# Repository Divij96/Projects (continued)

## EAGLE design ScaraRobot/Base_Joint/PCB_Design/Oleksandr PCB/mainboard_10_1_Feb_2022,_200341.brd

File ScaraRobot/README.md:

## Scara Robot
### Design and build-up of a 4 DoF SCARA like robot (3+1gripper), Intelligent machine design lab
- Mechanical models were designed using Autodesk inventor and built using 3dprinters
- The PCBs were designed using the Autodesk Eagle. They were later on manufactured
and soldered
- Each joint had an Absolute position encoder, a Torque sensor, a BLDC motor, a
gearbox, and a pair of Cross-Roller-Bearings. A master Linux PC with EtherCAT was
used for communication with the joint slaves
- The low-level control was implemented on the Microcontroller chip using C. A highlevel
control was implemented in MATLAB. EtherLab was used as a communication
interface
- The CDTM (Center for Digital Technology Management) supported us regarding the
team communication and project management aspects

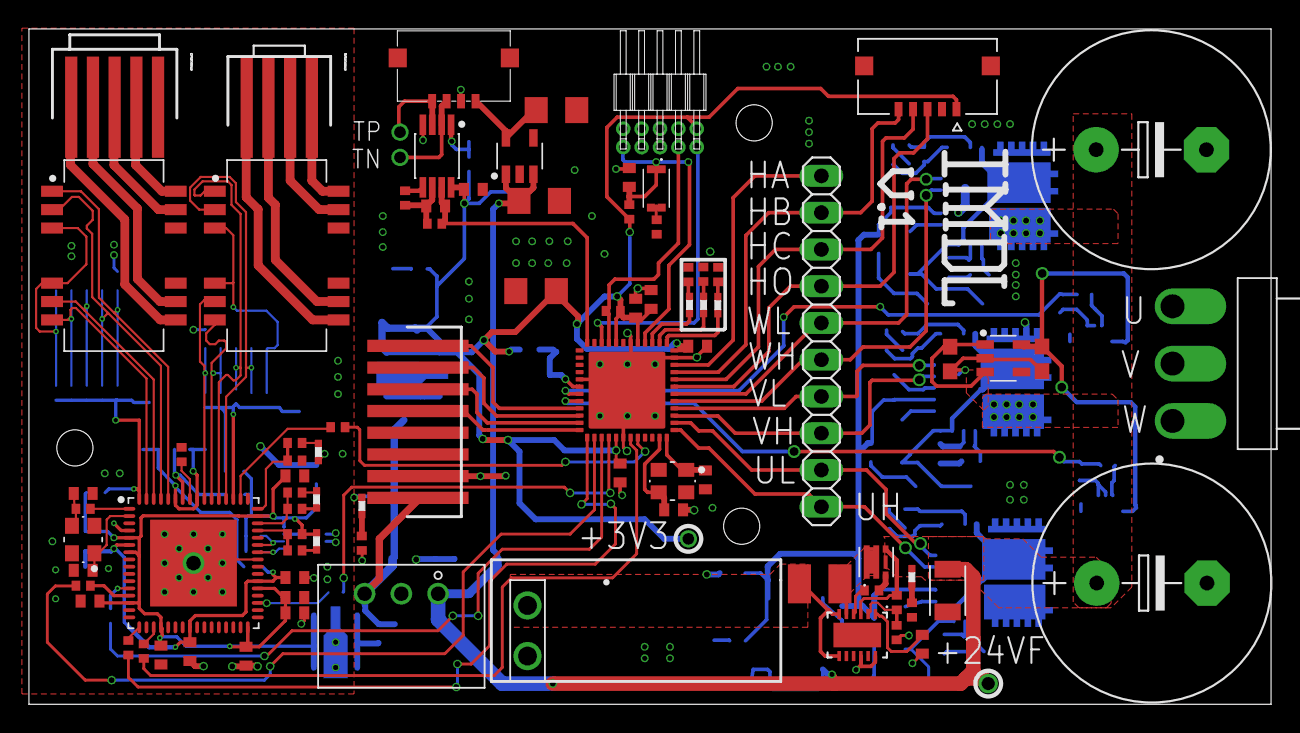
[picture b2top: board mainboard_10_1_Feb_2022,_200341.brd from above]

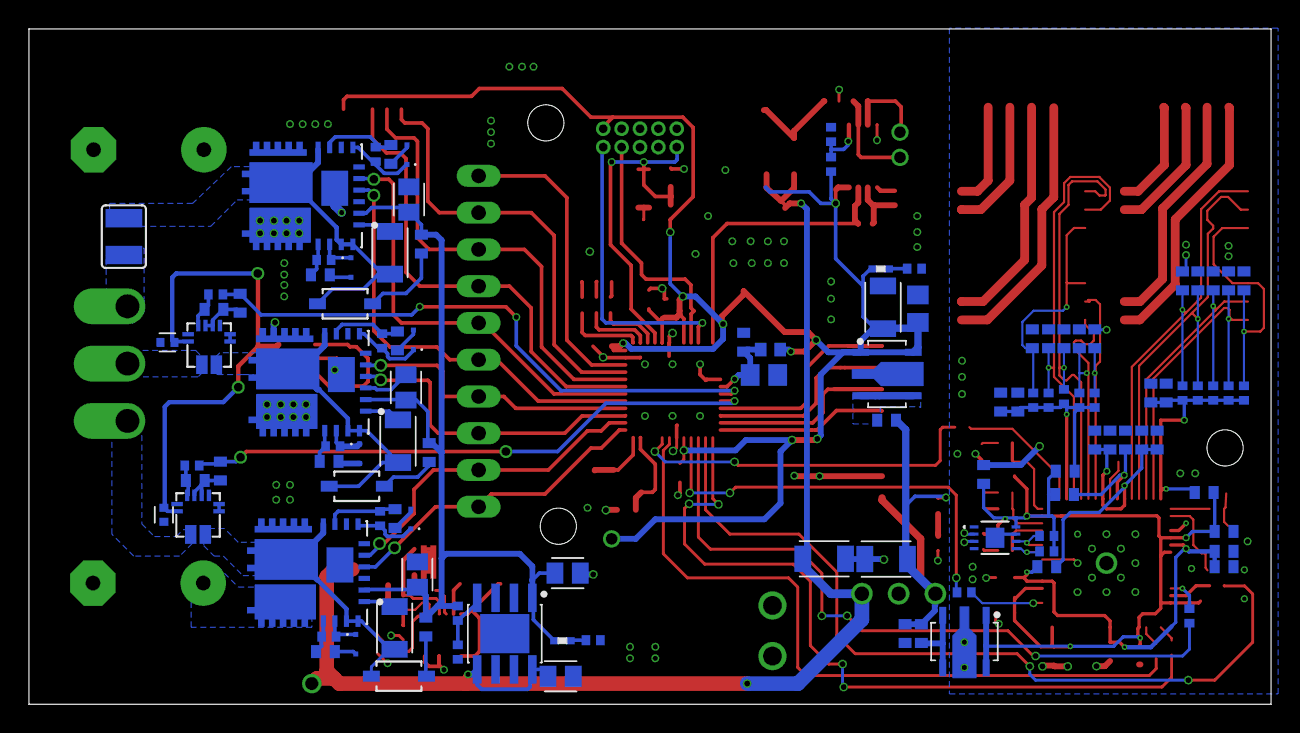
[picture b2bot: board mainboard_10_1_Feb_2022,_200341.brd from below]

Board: 2 copper layers, 85.8 x 46.7 mm, 194 parts (109 on the bottom side), 135 nets.

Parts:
AFE_TRQ1:C1: GCM155R71C683KA55; C0402
AFE_TRQ1:C2: GCM155R71C104JA55; C0402
AFE_TRQ1:IC1: MAX4208AUA+T; USOP8
AFE_TRQ1:R1: RT0402FRE07100RL; R0402
AFE_TRQ1:R2: RT0402BRD0712KL; R0402
AFE_TRQ1:R3: RT0402FRE0756KL; R0402
AFE_TRQ1:R4: RT0402BRD0710KL; R0402
ATSAMD:C4: GCM31CR71C106KA64; C1206
ATSAMD:C5, ATSAMD:C6: GCM21BR70J106KE22K; C0805
ATSAMD:C7, ATSAMD:C8, ATSAMD:C9, ATSAMD:C10, ATSAMD:C11, ATSAMD:C12: GCM155R71C104JA55; C0402
ATSAMD:C22, ATSAMD:C23: GCM1555C1H150FA16; C0402
ATSAMD:D1: QBLP595-IB; LED0402
ATSAMD:D2: QBLP595-O; LED0402
ATSAMD:D3: QBLP595-Y; LED0402
ATSAMD:IC2: ATSAMD51G18A-MUT; QFN48
ATSAMD:L1: BLM18EG221SN1D; BEADC1608X80
ATSAMD:R1, ATSAMD:R2, ATSAMD:R4: RT0402BRD0710KL; R0402
ATSAMD:R5: RT0402FRE07300RL; R0402
ATSAMD:R6: RT0402FRE0710KL; R0402
ATSAMD:R7: RT0402FRE071KL; R0402
ATSAMD:S2: USLPT2616CT2TR; USLPT2616CT
ATSAMD:Y2: ECX-2236
CURRENT_SENS:C1, CURRENT_SENS:C2: 0.1u; CAPC1005X60
CURRENT_SENS:C3, CURRENT_SENS:C4: GCM1555C1H510JA01; C0402
CURRENT_SENS:C5, CURRENT_SENS:C6: GCM155R71E223KA55; C0402
CURRENT_SENS:C7, CURRENT_SENS:C8: GCM188R71C105KA64; C0603
CURRENT_SENS:IC1, CURRENT_SENS:IC2: ACS70331EESATR-005B3; QFN12-ES
CURRENT_SENS:IC4: AP2204K-3.3TRG1; SOT-23-5
CURRENT_SENS:R3, CURRENT_SENS:R4: RT0402BRD071KL; R0402
CURRENT_SENS:SJ1: SJW
ETHERCAT1:C1, ETHERCAT1:C3, ETHERCAT1:C6, ETHERCAT1:C8, ETHERCAT1:C16: 1u; C0402
ETHERCAT1:C2, ETHERCAT1:C4, ETHERCAT1:C5, ETHERCAT1:C7, ETHERCAT1:C9, ETHERCAT1:C10, ETHERCAT1:C11, ETHERCAT1:C12, ETHERCAT1:C13, ETHERCAT1:C14, ETHERCAT1:C15, ETHERCAT1:C18, ETHERCAT1:C19, ETHERCAT1:C22: 100n; C0402
ETHERCAT1:C17: 470p; C0402
ETHERCAT1:C20, ETHERCAT1:C21: 18p; C0402
ETHERCAT1:C23, ETHERCAT1:C24, ETHERCAT1:C25, ETHERCAT1:C26, ETHERCAT1:C27, ETHERCAT1:C28, ETHERCAT1:C29, ETHERCAT1:C30: GCM1555C1H100JA16; C0402
ETHERCAT1:C31, ETHERCAT1:C32: 22n; C0402
ETHERCAT1:C33: GRM155C80J106ME11D; C0402
ETHERCAT1:C66: 1uF; C0402
ETHERCAT1:D1, ETHERCAT1:D2, ETHERCAT1:D3: QBLP595-IG; LED0402
ETHERCAT1:IC1: CAT24C512HU5IGT3; UDFN8
ETHERCAT1:IC2: RP115H331B-T1-FE; SOT-89-5
ETHERCAT1:L1, ETHERCAT1:L2, ETHERCAT1:L3, ETHERCAT1:L4, ETHERCAT1:L5: BLM15EG221SH1D; BEAD0402
ETHERCAT1:R1, ETHERCAT1:R16, ETHERCAT1:R17: 0R; R0402
ETHERCAT1:R2: 12k1; R0402
ETHERCAT1:R4, ETHERCAT1:R5: 4k7; R0402
ETHERCAT1:R6, ETHERCAT1:R24, ETHERCAT1:R25: 10k; R0402
ETHERCAT1:R7, ETHERCAT1:R26, ETHERCAT1:R27: RL1206FR-7WL; R0402
ETHERCAT1:R8, ETHERCAT1:R9, ETHERCAT1:R10, ETHERCAT1:R11, ETHERCAT1:R12, ETHERCAT1:R13, ETHERCAT1:R14, ETHERCAT1:R15: 49R9; R0402
ETHERCAT1:R18, ETHERCAT1:R19, ETHERCAT1:R20, ETHERCAT1:R21, ETHERCAT1:R22, ETHERCAT1:R23: 100; R0402
ETHERCAT1:T1, ETHERCAT1:T2: 749020100; SOIC127P965X533-16-TRAFO
ETHERCAT1:U1: LAN9252/ML; QFN64-T600
ETHERCAT1:X1: 87438-0443; 87438-04
ETHERCAT1:X3: 87438-0543; 87438-05
ETHERCAT1:Y1: ECX-2236
H1: 20021112-00010T4LF; 20021112-00010
INVERTER:C1, INVERTER:C3, INVERTER:C5: 10u 25V; CAPC2012X110
INVERTER:C2, INVERTER:C4, INVERTER:C6: 10u 50V; CAPC3216X135
INVERTER:C7, INVERTER:C8: 1mF; E7,5-16
INVERTER:CR1, INVERTER:CR2, INVERTER:CR3: 1N4148W-TPSOD123_MCC-M; SOD123_MCC-M
INVERTER:D2, INVERTER:D3, INVERTER:D4, INVERTER:D5, INVERTER:D7, INVERTER:D8: BAS3005A-02V_0; INFINEON_BAS3005A-02V_0
INVERTER:R1, INVERTER:R3, INVERTER:R7, INVERTER:R8, INVERTER:R11, INVERTER:R12: 100; R0402
INVERTER:R2, INVERTER:R4, INVERTER:R6, INVERTER:R9, INVERTER:R13, INVERTER:R15: 27; R0402
INVERTER:R5, INVERTER:R10, INVERTER:R14: 5.1; R0402
INVERTER:U$1, INVERTER:U$2, INVERTER:U$3: IRMS005-800MHTR; INFINEON_IRSM005-800MH_0
J1: 5037630591; MOLEX_5037630591
JP1: 1X10
M1: PST1,3/2-3,5; 1945096
POWER_UNIT:C1: GCM155R71E223KA55; C0402
POWER_UNIT:C2, POWER_UNIT:C3, POWER_UNIT:C4, POWER_UNIT:C6: 10u 50V; CAPC3216X135
POWER_UNIT:C5, POWER_UNIT:C9: GCM31CR71H225KA55; C1206
POWER_UNIT:C7, POWER_UNIT:C8: 2.2u; CAPC2012X110
POWER_UNIT:D1, POWER_UNIT:D2, POWER_UNIT:D3, POWER_UNIT:D4: QBLP595-IG; LED0402
POWER_UNIT:IC1: RP115H331B-T1-FE; SOT-89-5
POWER_UNIT:IC2: AP2204MP-ADJTRG1; SOIC127P600X170-9T271X340N
POWER_UNIT:IC3: AP2204K-3.3TRG1; SOT-23-5
POWER_UNIT:L5: BLM15EG221SH1D; BEAD0402
POWER_UNIT:PS2: R78E-1.0-5V; R78E-1.0
POWER_UNIT:Q1: DMN4020LFDE-7; TRANS_DMN4020LFDE-7
POWER_UNIT:R1: RT0402FRE07100RL; R0402
POWER_UNIT:R2: RT0402FRE07100KL; R0402
POWER_UNIT:R4: 10m; R1210
POWER_UNIT:R5: 11k; R0402
POWER_UNIT:R6, POWER_UNIT:R7, POWER_UNIT:R8, POWER_UNIT:R9, POWER_UNIT:R10: 1k; R0402
POWER_UNIT:R11: RT0402BRD074K99L; R0402
POWER_UNIT:U1: LT4356-1LINEAR_TECHNOLOGY_LT4356IDE-1#PBF_0_0; LINEAR_TECHNOLOGY_LT4356IDE-1#PBF_0
U$1: PTDA1,5/2-PH-3,5; 1725107
X2: B3PS-VH(LF)(SN)
X4: 87438-0843; 87438-08
X5: 5037630491

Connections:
+3V3: AFE_TRQ1:C2.1, AFE_TRQ1:IC1.8, AFE_TRQ1:R2.2, ATSAMD:C4.1, ATSAMD:C6.1, ATSAMD:C7.1, ATSAMD:C9.1, ATSAMD:C10.1, ATSAMD:C11.1, ATSAMD:IC2.17, ATSAMD:IC2.36, ATSAMD:IC2.41, ATSAMD:IC2.44, ATSAMD:L1.1, ATSAMD:R6.2, ATSAMD:R7.2, H1.1, J1.1, POWER_UNIT:C2.1, POWER_UNIT:D3.2, POWER_UNIT:IC1.1, POWER_UNIT:IC1.5
+5V: ETHERCAT1:C66.1, ETHERCAT1:L5.1, POWER_UNIT:C4.1, POWER_UNIT:D2.2, POWER_UNIT:L5.1, POWER_UNIT:PS2.3, X4.1
+5V_TRQ: POWER_UNIT:C9.1, POWER_UNIT:IC3.5, X5.1
+15V: INVERTER:C1.2, INVERTER:C3.2, INVERTER:C5.2, INVERTER:R5.2, INVERTER:R10.2, INVERTER:R14.2, INVERTER:U$1.2, INVERTER:U$2.2, INVERTER:U$3.2, POWER_UNIT:C8.1, POWER_UNIT:D4.2, POWER_UNIT:IC2.1, POWER_UNIT:R5.2
+24V: M1.1, POWER_UNIT:R4.2, POWER_UNIT:U1.6, POWER_UNIT:U1.7
+24V_F: CURRENT_SENS:C8.1, CURRENT_SENS:IC4.1, CURRENT_SENS:IC4.3, INVERTER:C7.+, INVERTER:C8.+, INVERTER:U$1.18-19-20-21-22-23, INVERTER:U$2.18-19-20-21-22-23, INVERTER:U$3.18-19-20-21-22-23, POWER_UNIT:C3.1, POWER_UNIT:C5.1, POWER_UNIT:C6.1, POWER_UNIT:C7.1, POWER_UNIT:D1.2, POWER_UNIT:IC2.5, POWER_UNIT:IC2.8, POWER_UNIT:IC3.1, POWER_UNIT:IC3.3, POWER_UNIT:PS2.1, POWER_UNIT:Q1.4_1, POWER_UNIT:Q1.4_2, POWER_UNIT:R2.2, POWER_UNIT:U1.3
AFE_TRQ1:ANAREF: AFE_TRQ1:IC1.1, AFE_TRQ1:R2.1, AFE_TRQ1:R4.2
AFE_TRQ1:N$1: AFE_TRQ1:IC1.5, AFE_TRQ1:R1.1
AFE_TRQ1:N$4: AFE_TRQ1:C1.2, AFE_TRQ1:IC1.6, AFE_TRQ1:R1.2, AFE_TRQ1:R3.1
ATSAMD:D1: ATSAMD:D1.2, ATSAMD:IC2.39
ATSAMD:D2: ATSAMD:D2.2, ATSAMD:IC2.37
ATSAMD:D3: ATSAMD:D3.2, ATSAMD:IC2.38
ATSAMD:N$1: ATSAMD:D3.1, ATSAMD:R4.1
ATSAMD:N$2: ATSAMD:D2.1, ATSAMD:R1.1
ATSAMD:N$12: ATSAMD:C5.1, ATSAMD:C8.1, ATSAMD:IC2.6, ATSAMD:L1.2
ATSAMD:N$13: ATSAMD:R5.2, ATSAMD:S2.2, ATSAMD:S2.4
ATSAMD:N$16: ATSAMD:D1.1, ATSAMD:R2.1
ATSAMD:XIN: ATSAMD:C22.2, ATSAMD:IC2.23, ATSAMD:Y2.3
ATSAMD:XOUT: ATSAMD:C23.2, ATSAMD:IC2.24, ATSAMD:Y2.1
CURRENT_SENS:+3V3_CURR: CURRENT_SENS:C1.2, CURRENT_SENS:C2.2, CURRENT_SENS:C7.1, CURRENT_SENS:IC1.12, CURRENT_SENS:IC2.12, CURRENT_SENS:IC4.5
CURRENT_SENS:U_OUT: CURRENT_SENS:C4.1, CURRENT_SENS:IC1.10, CURRENT_SENS:R3.2
CURRENT_SENS:V_OUT: CURRENT_SENS:C3.1, CURRENT_SENS:IC2.10, CURRENT_SENS:R4.2
ECAT_CS: ATSAMD:IC2.20, ETHERCAT1:R19.2
ECAT_MISO: ATSAMD:IC2.14, ETHERCAT1:R22.2
ECAT_MOSI: ATSAMD:IC2.13, ETHERCAT1:R23.2
ECAT_SCK: ATSAMD:IC2.19, ETHERCAT1:R18.2
ECAT_SQI2: ATSAMD:IC2.15, ETHERCAT1:R21.2
ECAT_SQI3: ATSAMD:IC2.16, ETHERCAT1:R20.2
ENC_MISO: ATSAMD:IC2.10, X4.7
ENC_MOSI: ATSAMD:IC2.9, X4.8
ENC_NCS: ATSAMD:IC2.11, X4.6
ENC_SCK: ATSAMD:IC2.12, X4.5
ETHERCAT1:#MISO: ETHERCAT1:R22.1, ETHERCAT1:U1.13
ETHERCAT1:#MOSI: ETHERCAT1:R23.1, ETHERCAT1:U1.17
ETHERCAT1:#SCK: ETHERCAT1:R18.1, ETHERCAT1:U1.19
ETHERCAT1:#SCS#: ETHERCAT1:R19.1, ETHERCAT1:U1.50
ETHERCAT1:#SQI2: ETHERCAT1:R21.1, ETHERCAT1:U1.12
ETHERCAT1:#SQI3: ETHERCAT1:R20.1, ETHERCAT1:U1.35
ETHERCAT1:+3V3: ETHERCAT1:C10.1, ETHERCAT1:C11.1, ETHERCAT1:C12.1, ETHERCAT1:C13.1, ETHERCAT1:C14.1, ETHERCAT1:C15.1, ETHERCAT1:C22.1, ETHERCAT1:C33.1, ETHERCAT1:D1.2, ETHERCAT1:IC1.8, ETHERCAT1:IC2.1, ETHERCAT1:IC2.5, ETHERCAT1:L1.1, ETHERCAT1:L2.1, ETHERCAT1:L3.1, ETHERCAT1:R4.2, ETHERCAT1:R5.2, ETHERCAT1:R6.2, ETHERCAT1:U1.5, ETHERCAT1:U1.7, ETHERCAT1:U1.14, ETHERCAT1:U1.20, ETHERCAT1:U1.32, ETHERCAT1:U1.37, ETHERCAT1:U1.47
ETHERCAT1:CT1: ETHERCAT1:C31.1, ETHERCAT1:R16.1, ETHERCAT1:T1.3, ETHERCAT1:T1.6
ETHERCAT1:CT2: ETHERCAT1:C32.1, ETHERCAT1:R17.1, ETHERCAT1:T2.3, ETHERCAT1:T2.6
ETHERCAT1:GPIO0: ETHERCAT1:R24.2, ETHERCAT1:R26.1, ETHERCAT1:U1.48
ETHERCAT1:GPIO1: ETHERCAT1:R25.2, ETHERCAT1:R27.1, ETHERCAT1:U1.46
ETHERCAT1:GPIO2: ETHERCAT1:R6.1, ETHERCAT1:R7.2, ETHERCAT1:U1.45
ETHERCAT1:I2C_SCL: ETHERCAT1:IC1.6, ETHERCAT1:R4.1, ETHERCAT1:U1.43
ETHERCAT1:I2C_SDA: ETHERCAT1:IC1.5, ETHERCAT1:R5.1, ETHERCAT1:U1.42
ETHERCAT1:IN_RX_N: ETHERCAT1:T1.9, ETHERCAT1:X1.4
ETHERCAT1:IN_RX_P: ETHERCAT1:T1.10, ETHERCAT1:X1.3
ETHERCAT1:IN_TX_N: ETHERCAT1:T1.15, ETHERCAT1:X1.2
ETHERCAT1:IN_TX_P: ETHERCAT1:T1.16, ETHERCAT1:X1.1
ETHERCAT1:N$1: ETHERCAT1:D2.2, ETHERCAT1:R26.2
ETHERCAT1:N$2: ETHERCAT1:D3.2, ETHERCAT1:R27.2
ETHERCAT1:N$3: ETHERCAT1:IC2.3, ETHERCAT1:IC2.4, ETHERCAT1:L5.2
ETHERCAT1:N$15: ETHERCAT1:D1.1, ETHERCAT1:R7.1
ETHERCAT1:OSCI: ETHERCAT1:R1.2, ETHERCAT1:U1.1
ETHERCAT1:OSCI1: ETHERCAT1:C20.2, ETHERCAT1:R1.1, ETHERCAT1:Y1.3
ETHERCAT1:OSCO: ETHERCAT1:C21.2, ETHERCAT1:U1.2, ETHERCAT1:Y1.1
ETHERCAT1:OUT_RX_N: ETHERCAT1:T2.9, ETHERCAT1:X3.5
ETHERCAT1:OUT_RX_P: ETHERCAT1:T2.10, ETHERCAT1:X3.4
ETHERCAT1:OUT_TX_N: ETHERCAT1:T2.15, ETHERCAT1:X3.3
ETHERCAT1:OUT_TX_P: ETHERCAT1:T2.16, ETHERCAT1:X3.2
ETHERCAT1:RBIAS: ETHERCAT1:R2.2, ETHERCAT1:U1.57
ETHERCAT1:RXA_N: ETHERCAT1:C24.1, ETHERCAT1:R10.1, ETHERCAT1:T1.8, ETHERCAT1:U1.54
ETHERCAT1:RXA_P: ETHERCAT1:C23.1, ETHERCAT1:R11.1, ETHERCAT1:T1.7, ETHERCAT1:U1.55
ETHERCAT1:RXB_N: ETHERCAT1:C28.1, ETHERCAT1:R14.1, ETHERCAT1:T2.2, ETHERCAT1:U1.61
ETHERCAT1:RXB_P: ETHERCAT1:C27.1, ETHERCAT1:R15.1, ETHERCAT1:T2.1, ETHERCAT1:U1.60
ETHERCAT1:TXA_N: ETHERCAT1:C26.1, ETHERCAT1:R8.1, ETHERCAT1:T1.2, ETHERCAT1:U1.52
ETHERCAT1:TXA_P: ETHERCAT1:C25.1, ETHERCAT1:R9.1, ETHERCAT1:T1.1, ETHERCAT1:U1.53
ETHERCAT1:TXB_N: ETHERCAT1:C30.1, ETHERCAT1:R12.1, ETHERCAT1:T2.8, ETHERCAT1:U1.63
ETHERCAT1:TXB_P: ETHERCAT1:C29.1, ETHERCAT1:R13.1, ETHERCAT1:T2.7, ETHERCAT1:U1.62
ETHERCAT1:VDD: ETHERCAT1:C16.1, ETHERCAT1:C17.1, ETHERCAT1:C18.1, ETHERCAT1:C19.1, ETHERCAT1:L4.1, ETHERCAT1:U1.6, ETHERCAT1:U1.24, ETHERCAT1:U1.38
ETHERCAT1:VDD12TX: ETHERCAT1:C6.1, ETHERCAT1:C7.1, ETHERCAT1:C8.1, ETHERCAT1:C9.1, ETHERCAT1:L4.2, ETHERCAT1:U1.56, ETHERCAT1:U1.59
ETHERCAT1:VDD33BIAS: ETHERCAT1:C5.1, ETHERCAT1:L3.2, ETHERCAT1:U1.58
ETHERCAT1:VDD33TXRX1: ETHERCAT1:C1.1, ETHERCAT1:C2.1, ETHERCAT1:L1.2, ETHERCAT1:R8.2, ETHERCAT1:R9.2, ETHERCAT1:R10.2, ETHERCAT1:R11.2, ETHERCAT1:R16.2, ETHERCAT1:U1.51
ETHERCAT1:VDD33TXRX2: ETHERCAT1:C3.1, ETHERCAT1:C4.1, ETHERCAT1:L2.2, ETHERCAT1:R12.2, ETHERCAT1:R13.2, ETHERCAT1:R14.2, ETHERCAT1:R15.2, ETHERCAT1:R17.2, ETHERCAT1:U1.64
GND: AFE_TRQ1:C2.2, AFE_TRQ1:IC1.4, AFE_TRQ1:R4.1, ATSAMD:C4.2, ATSAMD:C5.2, ATSAMD:C6.2, ATSAMD:C7.2, ATSAMD:C8.2, ATSAMD:C9.2, ATSAMD:C10.2, ATSAMD:C11.2, ATSAMD:C12.2, ATSAMD:C22.1, ATSAMD:C23.1, ATSAMD:IC2.5, ATSAMD:IC2.18, ATSAMD:IC2.35, ATSAMD:IC2.42, ATSAMD:IC2.EXP, ATSAMD:R1.2, ATSAMD:R2.2, ATSAMD:R4.2, ATSAMD:R5.1, CURRENT_SENS:C1.1, CURRENT_SENS:C2.1, CURRENT_SENS:C3.2, CURRENT_SENS:C4.2, CURRENT_SENS:C5.2, CURRENT_SENS:C6.2, CURRENT_SENS:C7.2, CURRENT_SENS:C8.2, CURRENT_SENS:IC1.5, CURRENT_SENS:IC1.6, CURRENT_SENS:IC1.8, CURRENT_SENS:IC1.9, CURRENT_SENS:IC1.11, CURRENT_SENS:IC2.5, CURRENT_SENS:IC2.6, CURRENT_SENS:IC2.8, CURRENT_SENS:IC2.9, CURRENT_SENS:IC2.11, CURRENT_SENS:IC4.2, ETHERCAT1:C1.2, ETHERCAT1:C2.2, ETHERCAT1:C3.2, ETHERCAT1:C4.2, ETHERCAT1:C5.2, ETHERCAT1:C6.2, ETHERCAT1:C7.2, ETHERCAT1:C8.2, ETHERCAT1:C9.2, ETHERCAT1:C10.2, ETHERCAT1:C11.2, ETHERCAT1:C12.2, ETHERCAT1:C13.2, ETHERCAT1:C14.2, ETHERCAT1:C15.2, ETHERCAT1:C16.2, ETHERCAT1:C17.2, ETHERCAT1:C18.2, ETHERCAT1:C19.2, ETHERCAT1:C20.1, ETHERCAT1:C21.1, ETHERCAT1:C22.2, ETHERCAT1:C23.2, ETHERCAT1:C24.2, ETHERCAT1:C25.2, ETHERCAT1:C26.2, ETHERCAT1:C27.2, ETHERCAT1:C28.2, ETHERCAT1:C29.2, ETHERCAT1:C30.2, ETHERCAT1:C31.2, ETHERCAT1:C32.2, ETHERCAT1:C33.2, ETHERCAT1:C66.2, ETHERCAT1:D2.1, ETHERCAT1:D3.1, ETHERCAT1:IC1.1, ETHERCAT1:IC1.2, ETHERCAT1:IC1.3, ETHERCAT1:IC1.4, ETHERCAT1:IC1.7, ETHERCAT1:IC1.9, ETHERCAT1:IC2.2, ETHERCAT1:R2.1, ETHERCAT1:R24.1, ETHERCAT1:R25.1, ETHERCAT1:U1.4, ETHERCAT1:U1.8, ETHERCAT1:U1.9, ETHERCAT1:U1.10, ETHERCAT1:U1.41, ETHERCAT1:U1.65, ETHERCAT1:Y1.2, ETHERCAT1:Y1.4, H1.3, H1.5, H1.9, INVERTER:C1.1, INVERTER:C3.1, INVERTER:C5.1, INVERTER:C7.-, INVERTER:C8.-, INVERTER:U$1.3, INVERTER:U$1.6, INVERTER:U$1.8, INVERTER:U$1.11-12-13-14-15, INVERTER:U$1.28, INVERTER:U$2.3, INVERTER:U$2.6, INVERTER:U$2.8, INVERTER:U$2.11-12-13-14-15, INVERTER:U$2.28, INVERTER:U$3.3, INVERTER:U$3.6, INVERTER:U$3.8, INVERTER:U$3.11-12-13-14-15, INVERTER:U$3.28, J1.2, M1.2, POWER_UNIT:C1.2, POWER_UNIT:C2.2, POWER_UNIT:C3.2, POWER_UNIT:C4.2, POWER_UNIT:C5.2, POWER_UNIT:C6.2, POWER_UNIT:C7.2, POWER_UNIT:C8.2, POWER_UNIT:C9.2, POWER_UNIT:IC1.2, POWER_UNIT:IC2.7, POWER_UNIT:IC2.9, POWER_UNIT:IC3.2, POWER_UNIT:PS2.2, POWER_UNIT:R6.1, POWER_UNIT:R7.1, POWER_UNIT:R8.1, POWER_UNIT:R9.1, POWER_UNIT:R10.1, POWER_UNIT:R11.1, POWER_UNIT:U1.10, POWER_UNIT:U1.12, X4.2, X5.2
HALL_A: ATSAMD:IC2.33, J1.5, JP1.9
HALL_B: ATSAMD:IC2.32, J1.4, JP1.8
HALL_C: ATSAMD:IC2.31, J1.3, JP1.7
HALL_O: ATSAMD:IC2.34, JP1.10
INVERTER:N$1: INVERTER:R3.2, INVERTER:R15.2, INVERTER:U$1.24
INVERTER:N$2: INVERTER:CR2.1, INVERTER:R5.1
INVERTER:N$3: INVERTER:D2.2, INVERTER:R15.1
INVERTER:N$4: INVERTER:C2.1, INVERTER:U$1.1
INVERTER:N$5: INVERTER:D3.1, INVERTER:R1.1, INVERTER:U$1.7
INVERTER:N$6: INVERTER:R1.2, INVERTER:R2.2, INVERTER:U$1.9
INVERTER:N$7: INVERTER:CR1.1, INVERTER:R10.1
INVERTER:N$8: INVERTER:D3.2, INVERTER:R2.1
INVERTER:N$9: INVERTER:CR3.1, INVERTER:R14.1
INVERTER:N$11: INVERTER:R6.2, INVERTER:R8.2, INVERTER:U$2.24
INVERTER:N$13: INVERTER:D2.1, INVERTER:R3.1, INVERTER:U$1.25
INVERTER:N$14: INVERTER:D4.1, INVERTER:R7.1, INVERTER:U$2.7
INVERTER:N$15: INVERTER:R4.2, INVERTER:R7.2, INVERTER:U$2.9
INVERTER:N$16: INVERTER:D4.2, INVERTER:R4.1
INVERTER:N$18: INVERTER:D5.1, INVERTER:R8.1, INVERTER:U$2.25
INVERTER:N$19: INVERTER:C4.1, INVERTER:U$2.1
INVERTER:N$21: INVERTER:D5.2, INVERTER:R6.1
INVERTER:N$25: INVERTER:R12.2, INVERTER:R13.2, INVERTER:U$3.24
INVERTER:N$26: INVERTER:D7.1, INVERTER:R11.1, INVERTER:U$3.7
INVERTER:N$27: INVERTER:R9.2, INVERTER:R11.2, INVERTER:U$3.9
INVERTER:N$28: INVERTER:D7.2, INVERTER:R9.1
INVERTER:N$30: INVERTER:D8.1, INVERTER:R12.1, INVERTER:U$3.25
INVERTER:N$31: INVERTER:C6.1, INVERTER:U$3.1
INVERTER:N$33: INVERTER:D8.2, INVERTER:R13.1
unnamed: CURRENT_SENS:IC1.3,4, INVERTER:C2.2, INVERTER:CR3.2, INVERTER:U$1.10, INVERTER:U$1.16-17, INVERTER:U$1.26, INVERTER:U$1.27
unnamed: CURRENT_SENS:IC2.3,4, INVERTER:C4.2, INVERTER:CR1.2, INVERTER:U$2.10, INVERTER:U$2.16-17, INVERTER:U$2.26, INVERTER:U$2.27
unnamed: CURRENT_SENS:SJ1.1, INVERTER:C6.2, INVERTER:CR2.2, INVERTER:U$3.10, INVERTER:U$3.16-17, INVERTER:U$3.26, INVERTER:U$3.27
NRESET: ATSAMD:C12.1, ATSAMD:IC2.40, ATSAMD:R6.1, ATSAMD:S2.1, ATSAMD:S2.3, H1.10
POWER_UNIT:N$1: POWER_UNIT:Q1.3, POWER_UNIT:R1.2
POWER_UNIT:N$2: POWER_UNIT:R1.1, POWER_UNIT:U1.4
POWER_UNIT:N$3: POWER_UNIT:Q1.1, POWER_UNIT:Q1.2, POWER_UNIT:Q1.5, POWER_UNIT:Q1.6, POWER_UNIT:R4.1, POWER_UNIT:U1.5
POWER_UNIT:N$4: POWER_UNIT:R2.1, POWER_UNIT:R11.2, POWER_UNIT:U1.2
POWER_UNIT:N$6: POWER_UNIT:D1.1, POWER_UNIT:R7.2
POWER_UNIT:N$7: POWER_UNIT:IC2.4, POWER_UNIT:R5.1, POWER_UNIT:R6.2
POWER_UNIT:N$8: POWER_UNIT:C1.1, POWER_UNIT:U1.1
POWER_UNIT:N$9: POWER_UNIT:D2.1, POWER_UNIT:R8.2
POWER_UNIT:N$10: POWER_UNIT:D3.1, POWER_UNIT:R9.2
POWER_UNIT:N$11: POWER_UNIT:D4.1, POWER_UNIT:R10.2
POWER_UNIT:N$12: POWER_UNIT:IC1.3, POWER_UNIT:IC1.4, POWER_UNIT:L5.2
SWCLK: ATSAMD:IC2.45, ATSAMD:R7.1, H1.4
SWDIO: ATSAMD:IC2.46, H1.2
TRQ_ADC: AFE_TRQ1:C1.1, AFE_TRQ1:IC1.7, AFE_TRQ1:R3.2, ATSAMD:IC2.48
TRQ_N: AFE_TRQ1:IC1.2, X5.3
TRQ_P: AFE_TRQ1:IC1.3, X5.4
U: CURRENT_SENS:IC1.1,2, X2.1
UH: ATSAMD:IC2.25, INVERTER:U$1.4, JP1.1
UL: ATSAMD:IC2.26, INVERTER:U$1.5, JP1.2
U_ADC: ATSAMD:IC2.8, CURRENT_SENS:C5.1, CURRENT_SENS:R3.1
V: CURRENT_SENS:IC2.1,2, X2.2
VH: ATSAMD:IC2.27, INVERTER:U$2.4, JP1.3
VL: ATSAMD:IC2.28, INVERTER:U$2.5, JP1.4
V_ADC: ATSAMD:IC2.7, CURRENT_SENS:C6.1, CURRENT_SENS:R4.1
W: CURRENT_SENS:SJ1.2, X2.3
WH: ATSAMD:IC2.29, INVERTER:U$3.4, JP1.5
WL: ATSAMD:IC2.30, INVERTER:U$3.5, JP1.6

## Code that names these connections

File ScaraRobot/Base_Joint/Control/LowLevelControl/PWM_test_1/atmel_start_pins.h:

/*
 * Code generated from Atmel Start.
 *
 * This file will be overwritten when reconfiguring your Atmel Start project.
 * Please copy examples or other code you want to keep to a separate file
 * to avoid losing it when reconfiguring.
 */
#ifndef ATMEL_START_PINS_H_INCLUDED
#define ATMEL_START_PINS_H_INCLUDED

#include <hal_gpio.h>

// SAMD51 has 14 pin functions

#define GPIO_PIN_FUNCTION_A 0
#define GPIO_PIN_FUNCTION_B 1
#define GPIO_PIN_FUNCTION_C 2
#define GPIO_PIN_FUNCTION_D 3
#define GPIO_PIN_FUNCTION_E 4
#define GPIO_PIN_FUNCTION_F 5
#define GPIO_PIN_FUNCTION_G 6
#define GPIO_PIN_FUNCTION_H 7
#define GPIO_PIN_FUNCTION_I 8
#define GPIO_PIN_FUNCTION_J 9
#define GPIO_PIN_FUNCTION_K 10
#define GPIO_PIN_FUNCTION_L 11
#define GPIO_PIN_FUNCTION_M 12
#define GPIO_PIN_FUNCTION_N 13

#define PA02 GPIO(GPIO_PORTA, 2)
#define PA03 GPIO(GPIO_PORTA, 3)
#define PA04 GPIO(GPIO_PORTA, 4)
#define PA05 GPIO(GPIO_PORTA, 5)
#define PA06 GPIO(GPIO_PORTA, 6)
#define PA08 GPIO(GPIO_PORTA, 8)
#define PA09 GPIO(GPIO_PORTA, 9)
#define ENC_CS GPIO(GPIO_PORTA, 14)
#define PA16 GPIO(GPIO_PORTA, 16)
#define PA17 GPIO(GPIO_PORTA, 17)
#define PA18 GPIO(GPIO_PORTA, 18)
#define PA19 GPIO(GPIO_PORTA, 19)
#define PA21 GPIO(GPIO_PORTA, 21)
#define PA22 GPIO(GPIO_PORTA, 22)
#define Hall_B GPIO(GPIO_PORTA, 23)
#define Hall_A GPIO(GPIO_PORTA, 24)
#define PB08 GPIO(GPIO_PORTB, 8)
#define PB10 GPIO(GPIO_PORTB, 10)
#define PB11 GPIO(GPIO_PORTB, 11)
#define Hall_C GPIO(GPIO_PORTB, 22)

#endif // ATMEL_START_PINS_H_INCLUDED

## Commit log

2022-03-29 added ros project
2022-04-05 changed folder location
2022-04-05 changed read me
2022-04-06 updated main read me
2022-04-06 updates for scara files
2022-04-14 added images
2022-04-14 pdf check
2022-04-14 pdf updates
2022-04-14 added control images
2022-04-14 added etherlab images
